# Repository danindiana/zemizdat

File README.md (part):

<div align="center">

# ZEMIZDAT

**Offline, identity-free exchange of short written "pamphlets" between strangers — over
nothing but Bluetooth broadcasts from cheap battery-powered devices.**

-success)

</div>

---

## Contents

1. [What this is](#1-what-this-is)
2. [The question, and the short answer](#2-the-question-and-the-short-answer)
3. [How it works](#3-how-it-works)
4. [What the evidence says](#4-what-the-evidence-says)
5. [What does not work (yet), and why](#5-what-does-not-work-yet-and-why)
6. [Repository map](#6-repository-map)
7. [Reproduce everything](#7-reproduce-everything)
8. [Hardware](#8-hardware)
9. [Related projects](#9-related-projects)
10. [Next step](#10-next-step)
11. [Evidence labels and honesty notes](#11-evidence-labels-and-honesty-notes)
12. [Diagrams](#12-diagrams)
13. [Status, licence, provenance](#13-status-licence-provenance)

---

## 1. What this is

ZEMIZDAT is a proposed pocket device inspired by *samizdat*, the hand-copied, hand-passed
literature of the Soviet era. Each device carries short texts — ideas, questions, arguments,
observations — called **pamphlets**. When devices come near each other they exchange pamphlets
over radio, with no internet, no phone network, no server, no account and no stable identity.
People carry pamphlets from room to room and district to district simply by walking around.

The system is **content-neutral**. It never decides what is true or acceptable. Each owner
decides what to publish, keep, delete and pass on.

This repository holds the complete pre-prototype engineering investigation
(mission brief: [`MISSION.md`](MISSION.md)):

* a formal model;
* four compared architectures;
* a byte-exact protocol specification;
* executable reference implementations in Python and C;
* a 377-run simulation campaign;
* an adversarial review;
* a hardware assessment;
* a falsifiable plan for the first hardware experiment.

> **Nothing here has been measured on hardware yet.** Every performance number is either
> *simulated* or *calculated*, and is labelled that way in the documents.

## 2. The question, and the short answer

> *Can thousands of independently operating, inexpensive, battery-powered devices exchange and
> propagate compact written information through spontaneous wireless encounters, while
> minimising duplicate storage, radio traffic, computation and dependence on centralised
> infrastructure?*

**Short answer: yes, conditionally.** The design is simpler than a mesh network, but some of
its limits are set by physics rather than engineering.

* **A connectionless broadcast "carousel" works.** There are no connections, keys, identities,
  routing or reconciliation protocol, and it serves everyone in range, including devices that
  never transmit. Simulated results:
  * 100 % of pamphlets within an hour in a hall of up to ~500 devices;
  * 95 % at 1 000 devices;
  * 98 % across six rooms of 500 people who walk between rooms;
  * 100 % across a simulated city of 3 000 people in 24 h.
* **A crowd adds receivers, not capacity.** One hall's shared airtime moves about 300 kB/s of
  pamphlet bytes. With 3 000 devices in one room, about 40 % of the collection reaches the
  average person in an hour.
* **Density-adaptive rate control is the indispensable mechanism.** Whether a real device can
  observe enough of the interference to run that control is **the largest open risk**.
* **Flooding is jamming, and interdiction beats majorities.** These are limits, not bugs, and
  they are proved or demonstrated in the repository.

Full verdict: [`09_final/EXECUTIVE_VERDICT.md`](09_final/EXECUTIVE_VERDICT.md).

## 3. How it works

### 3.1 Devices and modes

Each device has four owner-set permission bits — `RX`, `STORE`, `ORIG` (send my own), `FWD`
(send others') — exposed as three presets:

| Preset | Transmits | Receives | Privacy |
|---|---|---|---|
| **LISTEN** | never (passive scanning) | yes | discloses nothing — not even its presence |
| **EXCHANGE** | its own pamphlets | yes | discloses what it authored |
| **COURIER** | everything it carries | yes | discloses what it carries; bridges rooms and districts |

### 3.2 Content identity

A pamphlet is an immutable *canonical object* of at most 4 064 bytes (12-byte header, ordered
metadata, UTF-8 body). It is split into 220-byte chunks. Each chunk gets a truncated hash (a
*leaf*), and the pamphlet's identifier is the hash of its length and all its leaves. A small
**manifest** frame carries the leaves.

* A receiver can check **every chunk the moment it arrives**, so it can safely collect pieces
  from different senders, minutes or hours apart.
* A forged chunk is rejected on its own and can never spoil a reassembly.
* A pamphlet of up to 208 bytes is a single self-certifying frame.

### 3.3 The radio and the carousel

Frames of ≤ 236 bytes ride in anonymous, non-connectable BLE 5 *extended advertisements*, chained
three per event. Every device allowed to transmit runs a carousel with two modes:

* **Crowd mode** — many transmitters nearby. The device's event rate is scaled so the whole
  room's channel load stays near the optimum (primary-channel load ≈ 0.25, secondary ≈ 0.15).
  If it overhears someone else sending a pamphlet it holds, and the bytes match its own copy, it
  skips that pamphlet (*verified suppression*).
* **Burst mode** — eight transmitters or fewer, e.g. two people passing in a street. Contact
  time is the scarce resource, so the device listens continuously and sends fast.

Which pamphlet to send is weighted toward **items nobody nearby has sent recently**. Every
device can observe that locally, and it beat inventory-summary beacons in the simulations.

### 3.4 Receive path and storage

The receive path validates every field before touching any state, uses no heap, and holds
partial objects in at most 8 fixed staging slots. Completed objects are admitted (60 per minute
at most) and committed to a log-structured NOR-flash store. That store survives a power cut at
any byte, including during garbage collection — tested exhaustively.

### 3.5 Layers at a glance

Normative specification: [`03_protocol/ZEMIZDAT_PROTO_1.0.md`](03_protocol/ZEMIZDAT_PROTO_1.0.md)
and [`03_protocol/wire_format.md`](03_protocol/wire_format.md), which includes byte-exact worked
examples generated by the reference code.

## 4. What the evidence says

### 4.1 Executed (code in this repo, run in CI)

| Check | Result |
|---|---|
| Python reference: codec, reassembly, forged chunks, parser fuzz, storage | **31 tests pass** |
| Power cut at **every** programmed byte and erase, including GC | 0 corrupt, 0 duplicated records; at most one in-flight delete lost |
| C99 receive path vs Python on test vectors | **byte-identical** (8/8 objects, 46/46 duplicates rejected) |
| C fuzz: 2 000 000 mutated frames under AddressSanitizer + UBSan | 0 memory errors, 0 invalid completions |
| Receiver static RAM (4 slots) | 17 428 B |
| Simulator invariants (bookkeeping, determinism, LISTEN never transmits, collapse, partitions, capacity) | **14 tests pass** |
| XOR-fold inventory beacon (prior design) | one beacon reveals 100 % of a library at M = 300, 97 % at M = 1 000 → design replaced |

### 4.2 Simulated (`06_simulation`, 377 runs)

All numbers are mean completeness of honest receivers, listeners included.

| Scenario | HYBRID (this design) | rate-controlled broadcast | fixed-rate broadcast | pairwise anti-entropy |
|---|---|---|---|---|
| hall, 100 devices, 1 h | 1.00 | 1.00 | 1.00 | 0.80 (listeners 0) |
| hall, 1 000 devices, 1 h | **0.95** | 0.61 | 0.39 | 0.80 (listeners 0) |
| hall, 3 000 devices, 1 h | **0.40** | 0.36 | **0.00** | 0.28 (listeners 0) |
| 6 rooms × 500, walking, 1 h | **0.98** | 0.65 | — | 0.75 (listeners 0) |
| city of 3 000, 24 h | **1.00** (0.49 without burst mode) | 0.58 | — | 0.80 (listeners 0) |

Figures generated from the raw runs (`06_simulation/results/`):

### 4.3 Calculated (`04_mathematical_analysis/scripts`)

* An extended-advertising event is 3 × 136 µs primary pointers plus 1 064 µs per chained PDU on
  2M PHY. The optimal chain is ≈ 3 PDUs. One interference domain moves ≈ 1 500 frames/s
  (≈ 336 kB/s of pamphlet bytes), however many devices share it.
* Fixed-rate (10 Hz) advertising peaks at ~100 transmitters per domain and is dead by a few
  hundred.
* Receiving 3 000 one-KiB pamphlets in one dense hall takes **≥ 20–24 minutes even with perfect
  scheduling** at 30 % scan duty.
* Broadcast saves ≈ 100× in bits on air versus unicast — one copy per *reception tile*, not
  per person.

## 5. What does not work (yet), and why

| Limit | Kind | Where |
|---|---|---|
| Thousands in one room cannot all get everything quickly | physics (shared airtime) | [`communication_bounds.md`](04_mathematical_analysis/communication_bounds.md) |
| Rate control must sense interference it cannot decode; counting decodable neighbours only drops a 1 000-device hall from 0.82 to 0.47 | **open research question Q1** | [`RESEARCH_QUESTIONS.md`](09_final/RESEARCH_QUESTIONS.md) |
| A device that floods the channel is a jammer (20 % flooders → 0.29) | physics | [`counterexamples.md`](07_adversarial_review/counterexamples.md) |
| Anonymous publishing + finite storage + guaranteed retention is impossible | proved (Theorem D) | [`impossibility_results.md`](01_formal_model/impossibility_results.md) |
| Removing the few people who carry pamphlets between groups partitions the network, however cooperative everyone else is | proved + simulated | [`temporal_graphs.md`](04_mathematical_analysis/temporal_graphs.md) |
| Couriers are fingerprintable by what they carry; only LISTEN is library-private | proved | same |
| No device can know it holds "everything" | proved (Theorem G) | same |

## 6. Repository map

```
zemizdat/
├── README.md                       ← you are here
├── MISSION.md                      original brief (ZEMIZDAT-ARGON-1.0)
├── STATE.json                      machine-readable status, verdicts, open items
├── diagrams/                       12 diagrams (.dot source + .png + .svg)
├── 01_formal_model/                system definition, invariants I1–I10, liveness, impossibility A–J
├── 02_candidate_architectures/     broadcast, pairwise, hybrid, store-carry-forward,
│                                   comparison + verdicts, prior-art survey
├── 03_protocol/
│   ├── ZEMIZDAT_PROTO_1.0.md       normative spec
│   ├── wire_format.md              byte layouts + worked examples
│   ├── state_machine.md · synchronization.md · storage.md · security.md
│   ├── reference_py/               zmproto.py + 31 tests
│   └── reference_c/                zm_core.[ch], vectors, fuzz harness, Makefile
├── 04_mathematical_analysis/       bounds, temporal graphs, convergence, uncertainty
│   ├── scripts/                    airtime_model.py, sync_costs.py, xor_digest_attack.py
│   └── results/                    their JSON outputs
├── 05_hardware/                    UNO R4 WiFi, ESP32-S3, nRF52840, battery, BOM, dev boards
│   └── zb1/                        ZB-1 board design: spec, pinmap, BOM, Arduino variant, bring-up sketch
│       └── cad/                    KiCad 7 schematic + routed 4-layer PCB, Gerbers, STEP, renders, generators
├── 06_simulation/                  simulator.py, run_experiments.py, analyze.py,
│                                   tests/, configs/, results/ (runs.jsonl, summary.md, figures)
├── 07_adversarial_review/          threat model, 15 counterexamples, failure matrix, mitigations
├── 08_verification/                hardware test plan E1–E7, properties, acceptance tests, gaps
└── 09_final/                       verdict, architecture decision, spec index, research
                                    questions, prototype plan, next action, Gemini audit
```

**Suggested reading order:**

1. `09_final/EXECUTIVE_VERDICT.md`
2. `09_final/ARCHITECTURE_DECISION.md`
3. `03_protocol/ZEMIZDAT_PROTO_1.0.md`
4. `04_mathematical_analysis/convergence.md`
5. `07_adversarial_review/counterexamples.md`
6. `08_verification/test_plan.md`

## 7. Reproduce everything

Requirements: Python ≥ 3.11, `numpy ≥ 2`, `matplotlib`, `pytest`, and gcc or clang with
sanitizers; Graphviz only to re-render the diagrams.

```bash
git clone https://github.com/danindiana/zemizdat && cd zemizdat
pip install "numpy>=2" matplotlib pytest

# protocol reference (≈ 20 s)
(cd 03_protocol/reference_py && python -m pytest -q)

# C receive path: Python-generated vectors + 2M-frame sanitizer fuzz (≈ 1 min)
(cd 03_protocol/reference_c && make test)

# analytical models
(cd 04_mathematical_analysis/scripts && python airtime_model.py && python sync_costs.py && python xor_digest_attack.py)

# simulator tests (≈ 30 s), then the full campaign (≈ 6–8 CPU-hours, resumable)
cd 06_simulation
python -m pytest -q tests
python run_experiments.py --jobs 2     # appends to results/runs.jsonl, skips finished runs
python analyze.py                       # regenerates results/summary.md and figures

# one ad-hoc run
python simulator.py --N 1000 --T 1800 --strategy HYBRID --sdb false

# diagrams
cd ../diagrams && for f in *.dot; do dot -Tpng -Gdpi=160 "$f" -o "${f%.dot}.png" && dot -Tsvg "$f" -o "${f%.dot}.svg"; done
```

## 8. Hardware

| Option | Verdict | Why |
|---|---|---|
| Arduino UNO R4 WiFi | **reject for production**; bench helper | 32 KB SRAM on the RA4M1 and no radio; its ESP32-S3 can be flashed directly, and the RA4M1 can drive power-cut tests |
| ESP32-S3 | **conditional** (prototype) | fits easily; module datasheet gives BLE receive at 93 mA (peak), so ~2 days on 2000 mAh in a crowd |
| nRF52840 + 8 MB SPI NOR | **conditional** (production candidate) | radio ≈ 6.3 mA receive / 6.4 mA transmit at 0 dBm (datasheet); runs directly from a Li-ion cell |
| nRF54L15 | unresolved | datasheet figures not yet reviewed |

* Board shortlist with prices: [`05_hardware/dev_boards.md`](05_hardware/dev_boards.md).
  Best value is the Seeed XIAO nRF52840.
* Battery arithmetic, clearly marked as estimates:
  [`05_hardware/battery_budget.md`](05_hardware/battery_budget.md).

### ZB-1 development board (design, not yet built)

[`05_hardware/zb1/`](05_hardware/zb1/README.md) is a purpose-built Feather-size board:

* ESP32-S3-MINI-1-N8 (BLE 5 extended advertising, Wi-Fi, native USB, 8 MB NOR for the pamphlet log);
* USB-C LiPo charging (BQ21040) with a load-sharing power path and a 2 µA-Iq LDO;
* a power-switched 4-bit microSD slot (SDSC/SDHC/SDXC up to 2 TB; exFAT via SdFat or FAT32 reformat);
* test hooks for energy (E6) and power-cut (E7) experiments;
* ≈ $10–13 at qty 100 [estimate].

It is programmable from the Arduino IDE: a `boards.txt` entry and variant are included, and the
bring-up sketch (anonymous extended advertising + passive scan through `zm_core.c`) compiles.
Because ESP32-S3 BLE receive costs 93 mA versus 6.26 mA on the nRF52840, the design document
recommends an nRF52840-based ZB-2 for a pocket device.

The full CAD package is in [`05_hardware/zb1/cad/`](05_hardware/zb1/cad/README.md). It contains:

* a KiCad 7 schematic and a routed 4-layer PCB;
* Gerbers, drill, pick-and-place and BOM;
* a STEP model of the assembled board;
* the scripts that generate all of it from one design database.

## 9. Related projects

No open-source project found combines receive-only participation, no identity on air, and
content-addressed microcontroller firmware. The closest relatives are Rumble (epidemic
store-carry-forward on Android), Serval Rhizome/LBARD (content-addressed bundle sync over
constrained radios), bitchat (BLE mesh chat), Meshtastic and MeshCore (LoRa microcontroller
firmware), Reticulum LXMF (propagation nodes), and OpenHaystack (passive pickup of BLE
advertisements by bystanders).

Lessons from the security failures of comparable apps, notably Bridgefy and early bitchat, are
in [`02_candidate_architectures/prior_art.md`](02_candidate_architectures/prior_art.md).

## 10. Next step

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
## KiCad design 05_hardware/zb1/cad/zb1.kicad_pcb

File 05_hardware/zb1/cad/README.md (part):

# ZB-1 CAD package — KiCad 7 schematic, 4-layer PCB, fab outputs, 3D model

This folder holds the complete electronic CAD for the [ZB-1 development board](../README.md):

* a KiCad 7 project with schematic and routed 4-layer PCB;
* Gerbers, drill, pick-and-place and BOM;
* a STEP model of the assembled board, plus rendered views.

Everything is generated by scripts from one design database (`scripts/zb1_design.py`), so the
board can be rebuilt and every number below re-checked.

> **Licence:**
> * The ZB-1 hardware design is © 2026 Benjamin W. Denio under the
>   [CERN Open Hardware Licence v2 – Permissive](../../../LICENSES/CERN-OHL-P-2.0.txt).
> * The generator scripts in `scripts/` are under [Apache-2.0](../../../LICENSES/Apache-2.0.txt).
> * The Espressif module footprint and STEP model keep their CC-BY-SA 4.0 licence ([`lib/ATTRIBUTION.md`](lib/ATTRIBUTION.md)).
>
> If you modify the design and share it, say so in your copy (CERN-OHL-P §3.3).

> **Status: design files, not a proven board.** Nothing here has been fabricated, assembled or
> powered. The layout was placed by script and routed by an autorouter. DRC results are reported
> honestly in §5, including the items that still need a human. A qualified layout review is
> required before ordering boards; see the checklist in §7.

| | |
|---|---|
| Board | 50.8 × 22.86 mm (Adafruit Feather outline), 1.5 mm corner radius, 1.6 mm FR-4 |
| Layers | 4: F.Cu signal / In1 solid GND plane / In2 signal + GND fill / B.Cu signal + GND fill |
| Parts | 69 electrical parts + 2 mounting holes placed (7 of them DNP by default), top and bottom side |
| Routing | 1 127 track segments, 149 vias; 0.15 mm signal / 0.3 mm power / 0.2 mm USB tracks, 0.5/0.25 mm vias |
| Antenna | module antenna flush with the board edge; copper keep-out on all four layers past x = 45.4 mm |
| Netlist | schematic netlist checked pin by pin against the design database: **OK** — 69 components, 57 nets, 264 pin connections; the PCB pads were cross-checked the same way (0 mismatches) |
| DRC | **0 unconnected, 0 clearance / hole / short errors.** 8 mechanical items waived (mounting-hole courtyards, edge-mount microSD shell), 94 cosmetic warnings (silkscreen, library-copy differences) — see §5 |

## 1. Files

| Path | What it is |
|---|---|
| `zb1.kicad_pro`, `zb1.kicad_sch`, `zb1.kicad_pcb` | KiCad 7 project: open `zb1.kicad_pro` in KiCad 7.0 or newer |
| `lib/zb1.kicad_sym` | project symbols for parts KiCad 7 lacks: BQ21040, RT9080-33, DW01A, FS8205A, MAX17048 |
| `lib/zb1.pretty/ESP32-S3-MINI-1.kicad_mod` | module footprint from [espressif/kicad-libraries](https://github.com/espressif/kicad-libraries) (CC-BY-SA 4.0 with the KiCad design exception) |
| `lib/3dmodels/` | Espressif module STEP model, plus simple dimensioned envelope bodies for parts without a KiCad 3D model (USB-C, microSD, both JST connectors, KMR2 switches, crystal) |
| `fab/zb1_gerbers.zip` | Gerber X2 (11 layers) + Excellon drill (PTH and NPTH separate): upload this to a PCB fab |
| `fab/zb1_bom.csv` | grouped BOM with MPNs; DNP lines marked |
| `fab/zb1_pos.csv` | pick-and-place centroids, both sides, mm (DNP and through-hole parts excluded) |
| `docs/zb1_schematic.pdf` | schematic, one A2 sheet in seven titled blocks |
| `docs/zb1_assembly_top.pdf`, `docs/zb1_assembly_bottom.pdf` | assembly drawings (fab layer with every reference) |
| `docs/*drl_map.pdf` | drill maps |
| `3d/zb1.step` | whole assembly for enclosure/mechanical CAD (FreeCAD, Fusion, Onshape, SolidWorks) |
| `images/` | schematic PNG, per-copper-layer plots, board-surface images, 3D renders |
| `reports/drc.rpt` | full KiCad DRC report |
| `reports/netlist_check.txt` | schematic-vs-design-database check |
| `scripts/` | the generators (§6) |
| `build.sh` | rebuilds everything above from `scripts/zb1_design.py` |

## 2. Schematic

The schematic implements exactly the circuit in [`../README.md`](../README.md) §3–§5. It is drawn
in a "label per pin" style: every pin gets a short stub with its net label. It is generated from
`zb1_design.py`, so edit that file and regenerate rather than editing the schematic by hand.
`reports/netlist_check.txt` confirms that the netlist KiCad exports from the schematic matches the
database:
* every component present, with the designed footprint and value;
* every designed pin connection present;
* no extra connections.

Changes from the earlier text description, made while drawing it:

* **BQ21040 pinout** checked against the TI datasheet: 1 TS, 2 OUT, 3 /CHG, 4 ISET, 5 VSS, 6 IN.
  TS must not float (that enters a test mode), so R4 = 10 kΩ to GND stays fitted.
* **USBLC6-2SC6** is flow-through: pins 1/6 and 3/4 are the same line, so each data line is one net.
* **TPS22917 QOD** is tied to VOUT so the card's supply is actively discharged when switched off.
  CT is left open for the fastest turn-on.
* **Battery connector:** J3 pin 1 = BAT−, pin 2 = BAT+. Check this against your cell: JST-PH
  LiPo leads have no polarity standard, and a reversed cell will destroy the charger.
* **Optional cell protection:** U6 DW01A and Q2 FS8205A are drawn and laid out but DNP. SJ2
  bridges BATN to GND. Cut SJ2 if you fit them.

## 3. PCB

| Top | Bottom (seen from below) |
|---|---|
|  |  |

**Top side**
* ESP32-S3-MINI-1 with its antenna at the right-hand edge.
* USB-C at the left, with ESD protection.
* Charger and power-path parts.
* Vertical JST-PH battery jack.
* RESET and BOOT buttons.
* 32.768 kHz crystal placed against the module's XTAL_32K pins.
* Charge and user LEDs.
* Feather headers (supplied loose).

**Bottom side**
* microSD socket, slot at the USB end.
* SD load switch and pull-ups.
* LDO and the current-measurement jumper SJ1 (marked `CUT=I`).
* Battery divider.
* STEMMA-QT connector.
* Test pads TP1–TP5 for a pogo-pin fixture: TP_EN, VBAT, VSYS, 3V3, GND.
* Optional protection and fuel-gauge footprints.

| F.Cu | In1 (GND plane) |
|---|---|
|  |  |
| **In2** | **B.Cu** |
|  |  |

Layout decisions:

* **Antenna:**
  * The module sits flush with the board edge.
  * A rule area bans copper pour, tracks and vias on all four layers under and beyond the antenna (x > 45.4 mm).
  * No parts sit on either side in that zone.
* **No tracks under the module's centre on F.Cu.** A rule area 1.4 mm inside the pad ring allows
  only vias and the GND pour there. Pads may take a short inward stub to a via (standard practice
  for LGA modules, and needed to escape 0.85 mm-pitch pads). The centre GND pad has nine via-in-pad
  stitches to the In1 plane; specify them filled and capped, or tented from the bottom.
* **GND:**
  * In1 is an unbroken plane.
  * F.Cu, In2 and B.Cu are GND-filled with thermal reliefs.
  * Every SMD GND pad that had room received its own via to the plane before routing.
* **Mounting holes:**
  * Only the two antenna-end Feather holes (M2) are present.
  * The two USB-end holes collide with the microSD socket on the bottom and were omitted — a deliberate deviation from the Feather specification.
  * The antenna-end holes touch the module courtyard, exactly as on Adafruit's own ESP32-S3 Feather.
* **Silkscreen:**
  * Feather pin names on the top.
  * Battery polarity marks, button names and board name on the top.
  * Passive references only on the assembly drawings, to keep the silkscreen legible.
  * No serial numbers or unique identifiers ([`../README.md`](../README.md) R8).

### Design rules used

Set for a standard 4-layer prototype service (JLCPCB/PCBWay class): track/space 0.15/0.15 mm
signal (fab minimum is typically 0.09–0.1 mm), 0.3 mm power, via 0.5 mm pad / 0.25 mm drill,
hole-to-copper 0.2 mm, copper-to-edge 0.25 mm. **Check the 0.25 mm drill against your fab's
standard (not premium) capability before ordering.**

## 4. 3D model

`3d/zb1.step` contains the bare board and every fitted part:
* the real Espressif module model;
* KiCad library models for the passives, ICs and headers;
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
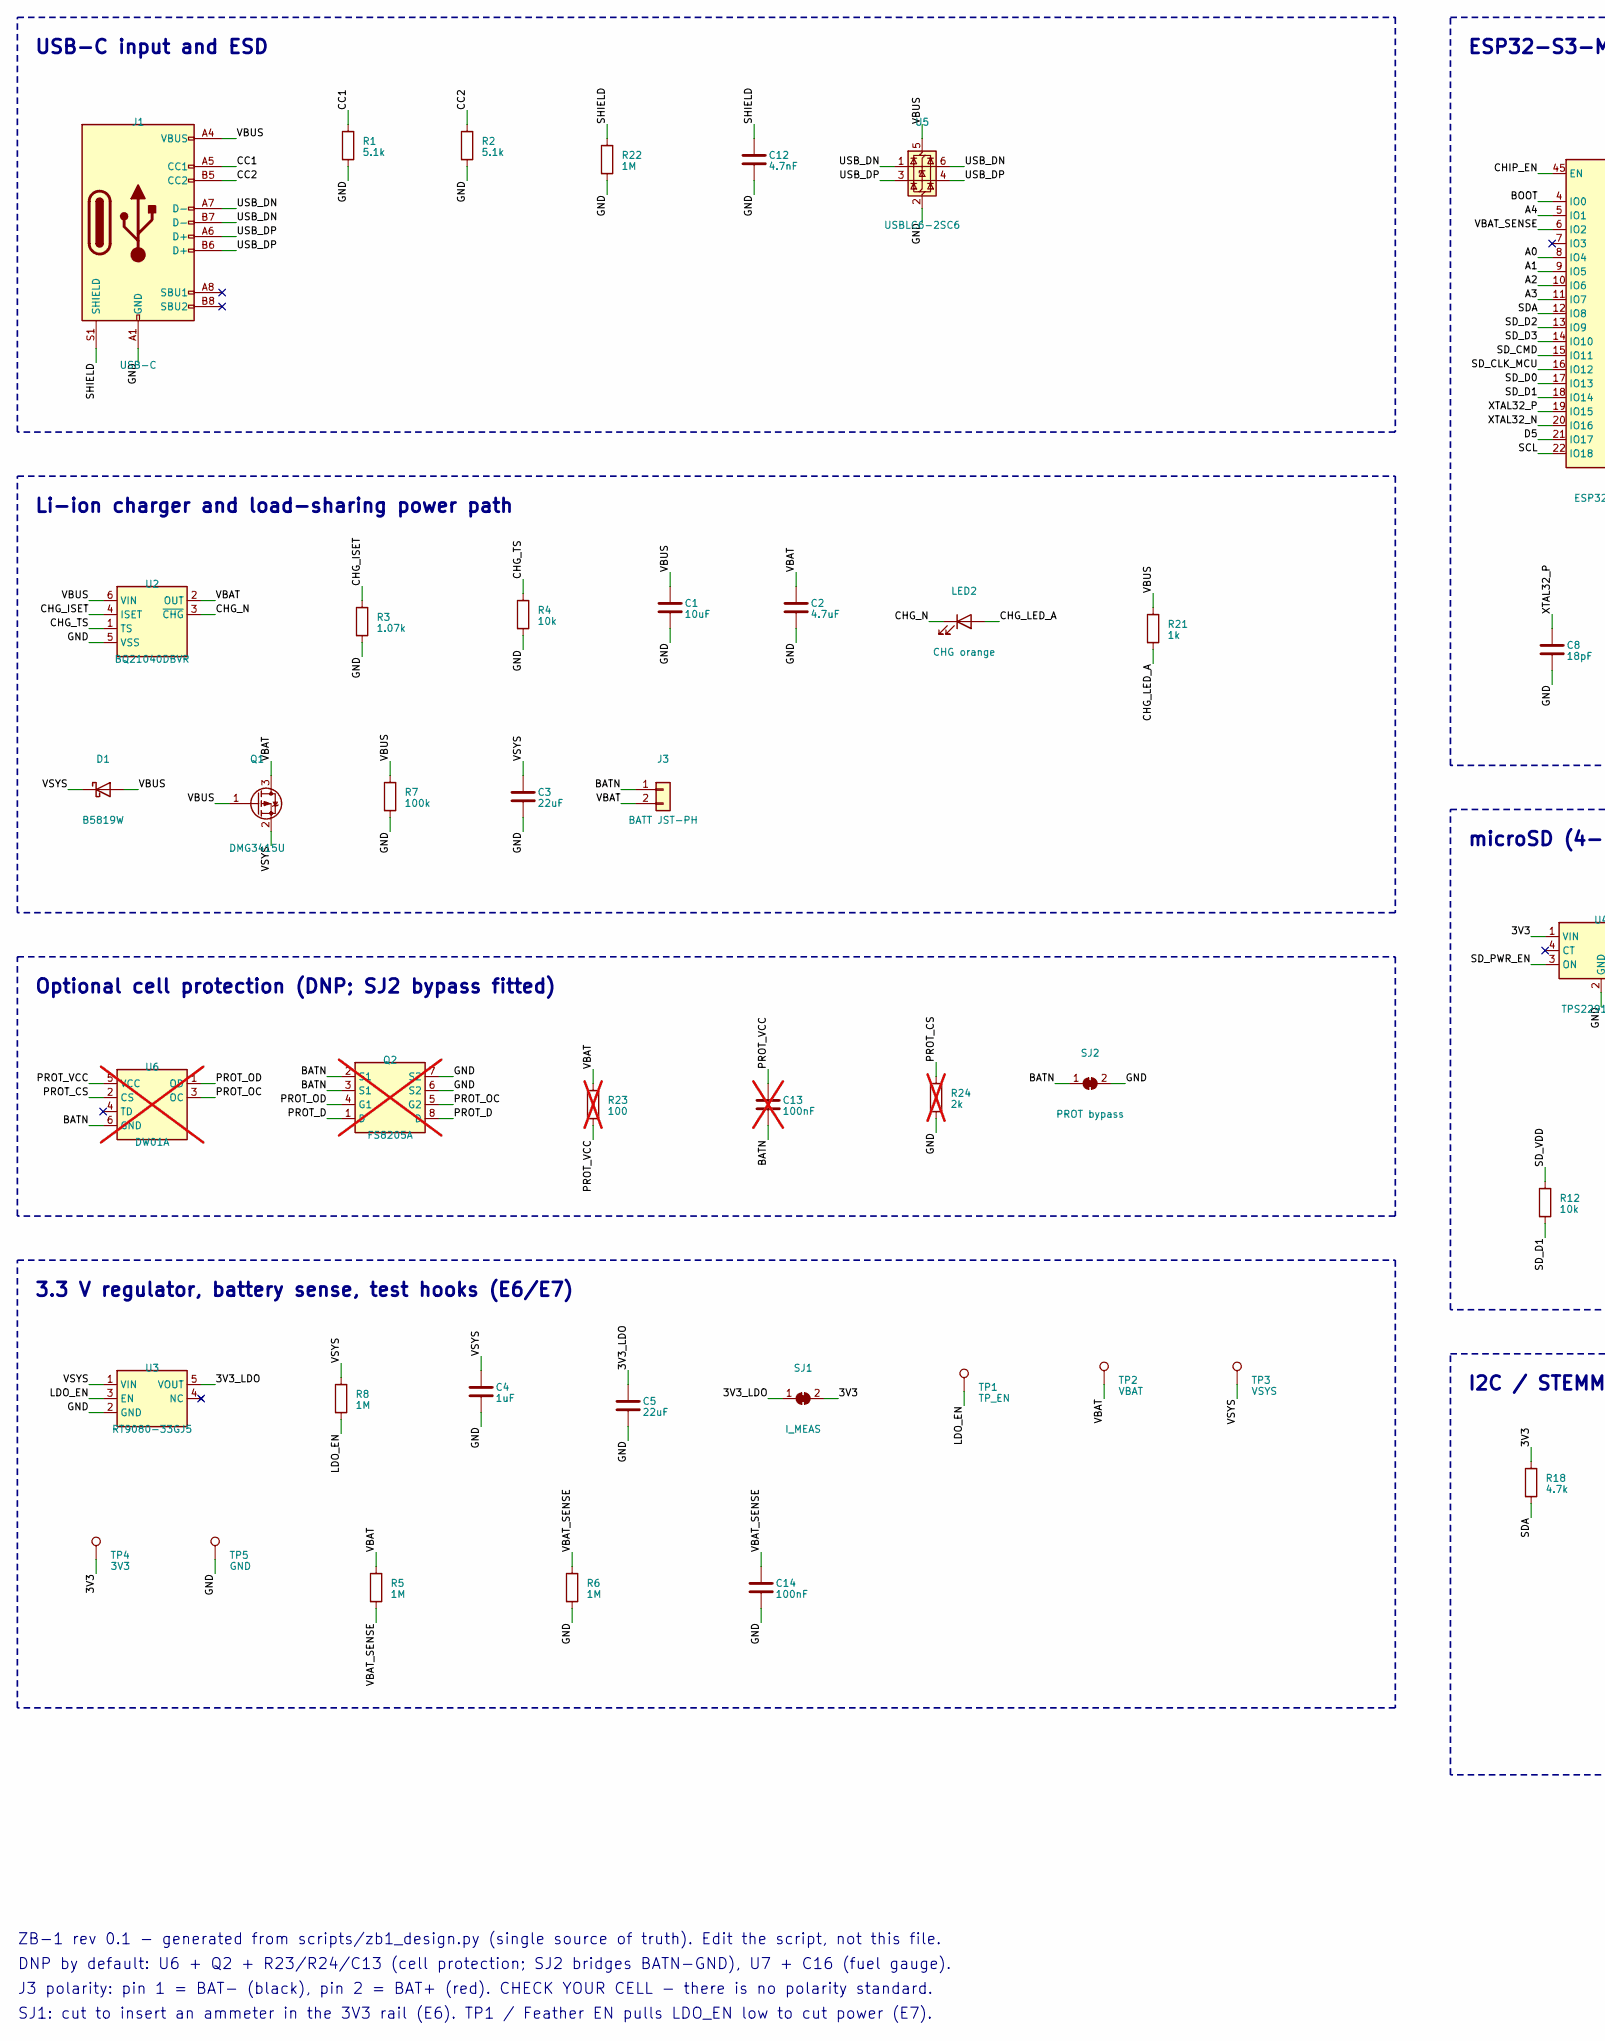
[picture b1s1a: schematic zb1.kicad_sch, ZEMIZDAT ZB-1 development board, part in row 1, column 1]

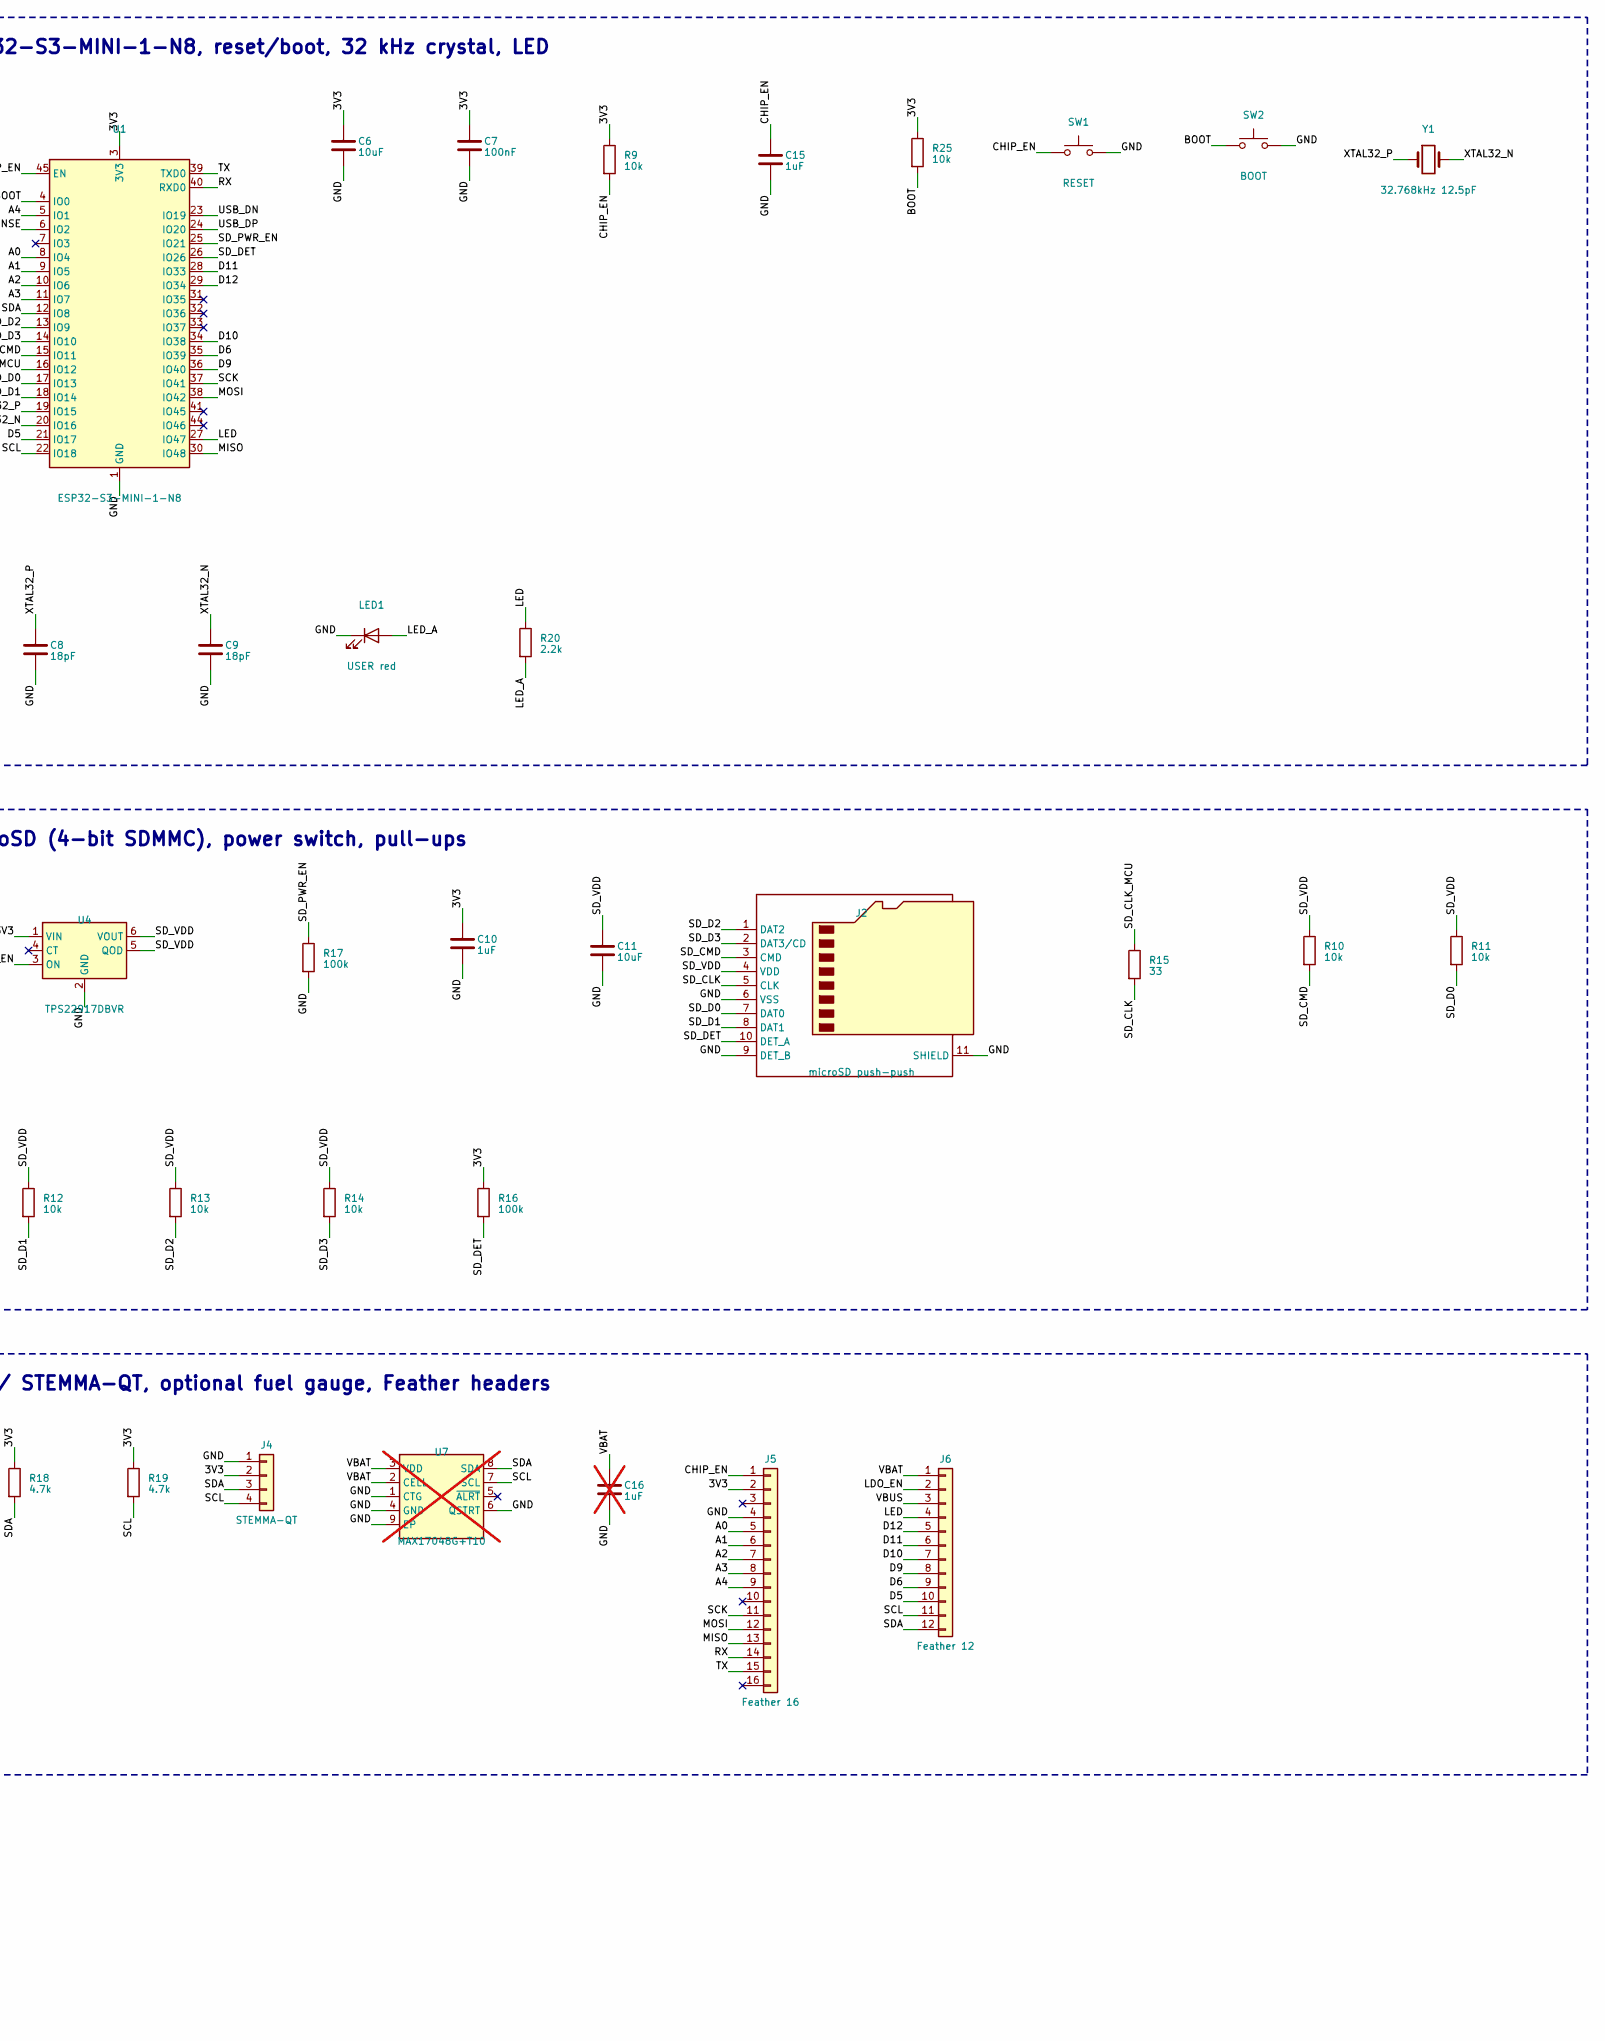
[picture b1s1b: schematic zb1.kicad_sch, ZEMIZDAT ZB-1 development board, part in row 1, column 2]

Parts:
C1, C6, C11: 10uF; C_0603_1608Metric; MPN 10uF X5R/X7R
C2: 4.7uF; C_0603_1608Metric; MPN 4.7uF X5R/X7R
C3, C5: 22uF; C_0805_2012Metric; MPN 22uF X5R/X7R
C4, C10, C15: 1uF; C_0402_1005Metric; MPN 1uF X5R/X7R
C7, C14: 100nF; C_0402_1005Metric; MPN 100nF X5R/X7R
C8, C9: 18pF; C_0402_1005Metric; MPN 18pF C0G
C12: 4.7nF; C_0402_1005Metric; MPN 4.7nF X5R/X7R
C13: 100nF; C_0402_1005Metric; MPN 100nF X5R/X7R; not fitted
C16: 1uF; C_0402_1005Metric; MPN 1uF X5R/X7R; not fitted
D1: B5819W; D_SOD-123; MPN B5819W SOD-123
J1: USB-C; USB_C_Receptacle_HRO_TYPE-C-31-M-12; MPN HRO TYPE-C-31-M-12
J2: microSD push-push; microSD_HC_Hirose_DM3AT-SF-PEJM5; MPN Hirose DM3AT-SF-PEJM5
J3: BATT JST-PH; JST_PH_B2B-PH-SM4-TB_1x02-1MP_P2.00mm_Vertical; MPN JST B2B-PH-SM4-TB
J4: STEMMA-QT; JST_SH_BM04B-SRSS-TB_1x04-1MP_P1.00mm_Vertical; MPN JST BM04B-SRSS-TB
J5: Feather 16; PinHeader_1x16_P2.54mm_Vertical; MPN 1x16 2.54mm header (ship loose)
J6: Feather 12; PinHeader_1x12_P2.54mm_Vertical; MPN 1x12 2.54mm header (ship loose)
LED1: USER red; LED_0603_1608Metric; MPN red 0603 LED
LED2: CHG orange; LED_0603_1608Metric; MPN orange 0603 LED
Q1: DMG3415U; SOT-23; MPN Diodes DMG3415U-7
Q2: FS8205A; TSSOP-8_4.4x3mm_P0.65mm; MPN Fortune FS8205A; not fitted
R1, R2: 5.1k; R_0402_1005Metric; MPN 5.1k 1% 0402
R3: 1.07k; R_0402_1005Metric; MPN 1.07k 1% 0402
R4: 10k; R_0402_1005Metric; MPN 10k 1% (or 10k NTC on the cell)
R5, R6, R8, R22: 1M; R_0402_1005Metric; MPN 1M 1% 0402
R7, R16, R17: 100k; R_0402_1005Metric; MPN 100k 1% 0402
R9, R10, R11, R12, R13, R14, R25: 10k; R_0402_1005Metric; MPN 10k 1% 0402
R15: 33; R_0402_1005Metric; MPN 33 1% 0402
R18, R19: 4.7k; R_0402_1005Metric; MPN 4.7k 1% 0402
R20: 2.2k; R_0402_1005Metric; MPN 2.2k 1% 0402
R21: 1k; R_0402_1005Metric; MPN 1k 1% 0402
R23: 100; R_0402_1005Metric; MPN 100 1% 0402; not fitted
R24: 2k; R_0402_1005Metric; MPN 2k 1% 0402; not fitted
SJ1: I_MEAS; SolderJumper-2_P1.3mm_Bridged_RoundedPad1.0x1.5mm; MPN (PCB) cut to measure current
SJ2: PROT bypass; SolderJumper-2_P1.3mm_Bridged_RoundedPad1.0x1.5mm; MPN (PCB) cut if U6/Q2 fitted
SW1: RESET; SW_Push_1P1T_NO_CK_KMR2; MPN C&K KMR221GLFS
SW2: BOOT; SW_Push_1P1T_NO_CK_KMR2; MPN C&K KMR221GLFS
TP1: TP_EN; TestPoint_Pad_D1.0mm; MPN (PCB)
TP2: VBAT; TestPoint_Pad_D1.0mm; MPN (PCB)
TP3: VSYS; TestPoint_Pad_D1.0mm; MPN (PCB)
TP4: 3V3; TestPoint_Pad_D1.0mm; MPN (PCB)
TP5: GND; TestPoint_Pad_D1.0mm; MPN (PCB)
U1: ESP32-S3-MINI-1-N8; ESP32-S3-MINI-1; MPN Espressif ESP32-S3-MINI-1-N8
U2: BQ21040DBVR; SOT-23-6; MPN TI BQ21040DBVR
U3: RT9080-33GJ5; SOT-23-5; MPN Richtek RT9080-33GJ5
U4: TPS22917DBVR; SOT-23-6; MPN TI TPS22917DBVR
U5: USBLC6-2SC6; SOT-23-6; MPN ST USBLC6-2SC6
U6: DW01A; SOT-23-6; MPN Fortune DW01A; not fitted
U7: MAX17048G+T10; TDFN-8-1EP_2x2mm_P0.5mm_EP0.8x1.2mm; MPN Analog Devices MAX17048G+T10; not fitted
Y1: 32.768kHz 12.5pF; Crystal_SMD_3215-2Pin_3.2x1.5mm; MPN Epson FC-135 32.768kHz 12.5pF

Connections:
3V3: C6.1, C7.1, C10.1, J4.2, J5.2, R9.1, R16.1, R18.1, R19.1, R25.1, SJ1.2 (B), TP4.1, U1.3 (3V3), U4.1 (VIN)
3V3_LDO: C5.1, SJ1.1 (A), U3.5 (VOUT)
A0: J5.5, U1.8 (IO4)
A1: J5.6, U1.9 (IO5)
A2: J5.7, U1.10 (IO6)
A3: J5.8, U1.11 (IO7)
A4: J5.9, U1.5 (IO1)
BATN: C13.2, J3.1, Q2.2 (S1), Q2.3 (S1), SJ2.1 (A), U6.6 (GND)
BOOT: R25.2, SW2.1, U1.4 (IO0)
CC1: J1.A5 (CC1), R1.1
CC2: J1.B5 (CC2), R2.1
CHG_ISET: R3.1, U2.4 (ISET)
CHG_LED_A: LED2.2 (A), R21.2
CHG_N: LED2.1 (K), U2.3 (~CHG)
CHG_TS: R4.1, U2.1 (TS)
CHIP_EN: C15.1, J5.1, R9.2, SW1.1, U1.45 (EN)
D5: J6.10, U1.21 (IO17)
D6: J6.9, U1.35 (IO39)
D9: J6.8, U1.36 (IO40)
D10: J6.7, U1.34 (IO38)
D11: J6.6, U1.28 (IO33)
D12: J6.5, U1.29 (IO34)
GND: C1.2, C2.2, C3.2, C4.2, C5.2, C6.2, C7.2, C8.2, C9.2, C10.2, C11.2, C12.2, C14.2, C15.2, C16.2, J1.A1 (GND), J1.A12 (GND), J1.B1 (GND), J1.B12 (GND), J2.6 (VSS), J2.9 (DET_B), J2.11 (SHIELD), J4.1, J5.4, LED1.1 (K), Q2.6 (S2), Q2.7 (S2), R1.2, R2.2, R3.2, R4.2, R6.2, R7.2, R17.2, R22.2, R24.2, SJ2.2 (B), SW1.2, SW2.2, TP5.1, U1.1 (GND), U1.2 (GND), U1.42 (GND), U1.43 (GND), U1.46 (GND), U1.47 (GND), U1.48 (GND), U1.49 (GND), U1.50 (GND), U1.51 (GND), U1.52 (GND), U1.53 (GND), U1.54 (GND), U1.55 (GND), U1.56 (GND), U1.57 (GND), U1.58 (GND), U1.59 (GND), U1.60 (GND), U1.61 (GND), U1.62 (GND), U1.63 (GND), U1.64 (GND), U1.65 (GND), U2.5 (VSS), U3.2 (GND), U4.2 (GND), U5.2 (GND), U7.1 (CTG), U7.4 (GND), U7.6 (QSTRT), U7.9 (EP)
LDO_EN: J6.2, R8.2, TP1.1, U3.3 (EN)
LED: J6.4, R20.1, U1.27 (IO47)
LED_A: LED1.2 (A), R20.2
MISO: J5.13, U1.30 (IO48)
MOSI: J5.12, U1.38 (IO42)
PROT_CS: R24.1, U6.2 (CS)
PROT_D: Q2.1 (D), Q2.8 (D)
PROT_OC: Q2.5 (G2), U6.3 (OC)
PROT_OD: Q2.4 (G1), U6.1 (OD)
PROT_VCC: C13.1, R23.2, U6.5 (VCC)
RX: J5.14, U1.40 (RXD0)
SCK: J5.11, U1.37 (IO41)
SCL: J4.4, J6.11, R19.2, U1.22 (IO18), U7.7 (SCL)
SDA: J4.3, J6.12, R18.2, U1.12 (IO8), U7.8 (SDA)
SD_CLK: J2.5 (CLK), R15.2
SD_CLK_MCU: R15.1, U1.16 (IO12)
SD_CMD: J2.3 (CMD), R10.2, U1.15 (IO11)
SD_D0: J2.7 (DAT0), R11.2, U1.17 (IO13)
SD_D1: J2.8 (DAT1), R12.2, U1.18 (IO14)
SD_D2: J2.1 (DAT2), R13.2, U1.13 (IO9)
SD_D3: J2.2 (DAT3/CD), R14.2, U1.14 (IO10)
SD_DET: J2.10 (DET_A), R16.2, U1.26 (IO26)
SD_PWR_EN: R17.1, U1.25 (IO21), U4.3 (ON)
SD_VDD: C11.1, J2.4 (VDD), R10.1, R11.1, R12.1, R13.1, R14.1, U4.5 (QOD), U4.6 (VOUT)
SHIELD: C12.1, J1.S1 (SHIELD), R22.1
TX: J5.15, U1.39 (TXD0)
USB_DN: J1.A7 (D-), J1.B7 (D-), U1.23 (IO19), U5.1 (I/O1), U5.6 (I/O1)
USB_DP: J1.A6 (D+), J1.B6 (D+), U1.24 (IO20), U5.3 (I/O2), U5.4 (I/O2)
VBAT: C2.1, C16.1, J3.2, J6.1, Q1.3 (D), R5.1, R23.1, TP2.1, U2.2 (OUT), U7.2 (CELL), U7.3 (VDD)
VBAT_SENSE: C14.1, R5.2, R6.1, U1.6 (IO2)
VBUS: C1.1, D1.2 (A), J1.A4 (VBUS), J1.A9 (VBUS), J1.B4 (VBUS), J1.B9 (VBUS), J6.3, Q1.1 (G), R7.1, R21.1, U2.6 (VIN), U5.5 (VBUS)
VSYS: C3.1, C4.1, D1.1 (K), Q1.2 (S), R8.1, TP3.1, U3.1 (VIN)
XTAL32_N: C9.1, U1.20 (IO16), Y1.2
XTAL32_P: C8.1, U1.19 (IO15), Y1.1

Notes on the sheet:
USB-C input and ESD
Li-ion charger and load-sharing power path
Optional cell protection (DNP; SJ2 bypass fitted)
3.3 V regulator, battery sense, test hooks (E6/E7)
ESP32-S3-MINI-1-N8, reset/boot, 32 kHz crystal, LED
microSD (4-bit SDMMC), power switch, pull-ups
I2C / STEMMA-QT, optional fuel gauge, Feather headers
ZB-1 rev 0.1 - generated from scripts/zb1_design.py (single source of truth). Edit the script, not this file.
DNP by default: U6 + Q2 + R23/R24/C13 (cell protection; SJ2 bridges BATN-GND), U7 + C16 (fuel gauge).
J3 polarity: pin 1 = BAT- (black), pin 2 = BAT+ (red). CHECK YOUR CELL - there is no polarity standard.
SJ1: cut to insert an ammeter in the 3V3 rail (E6). TP1 / Feather EN pulls LDO_EN low to cut power (E7).

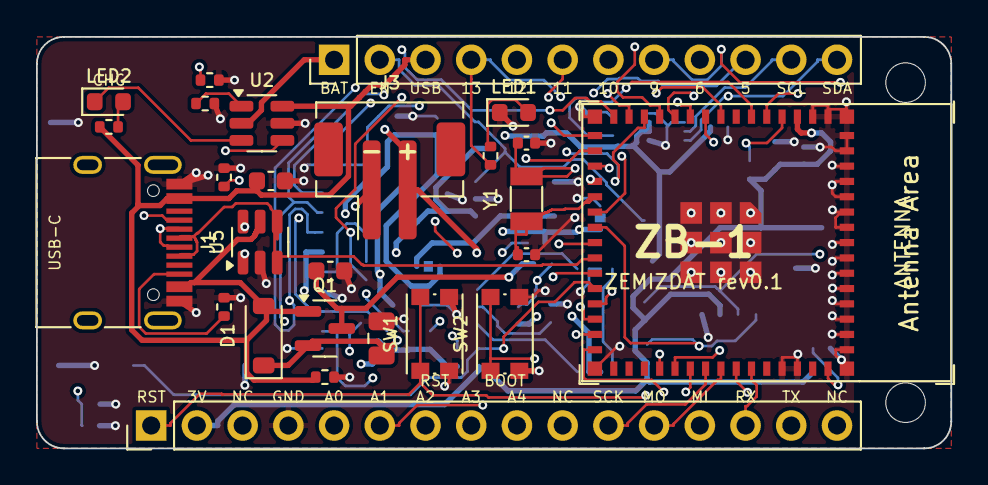
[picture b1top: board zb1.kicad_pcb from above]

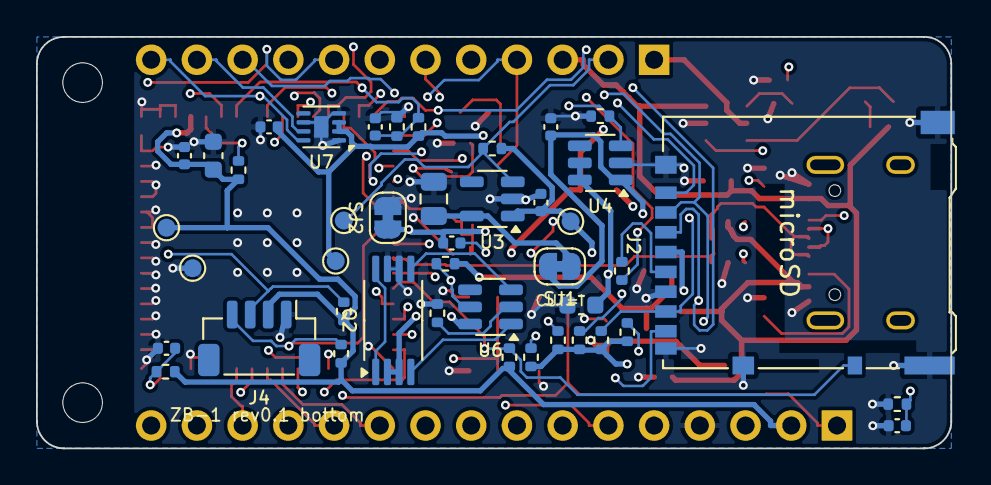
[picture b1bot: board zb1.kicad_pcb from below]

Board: 4 copper layers, 50.8 x 22.9 mm, 71 parts (43 on the bottom side), 57 nets.

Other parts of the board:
H3, H4: M2; MountingHole_2.2mm_M2

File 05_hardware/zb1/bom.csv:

ref,qty,part,package,function,unit_usd_qty100,price_basis,populate
U1,1,ESP32-S3-MINI-1-N8,module 15.4x20.5 mm,MCU + BLE 5 + Wi-Fi + 8 MB flash + PCB antenna,2.90,estimate,yes
U2,1,TI BQ21040DBVR,SOT-23-6,1-cell Li-ion linear charger (ISET 500 mA; TS input; /CHG),0.55,estimate,yes
U3,1,Richtek RT9080-33GJ5,SOT-23-5,3.3 V 600 mA LDO; 2 uA Iq; EN broken out for power-cut tests,0.20,estimate,yes
U4,1,TI TPS22917DBVR,SOT-23-6,microSD power load switch (1 uA leakage off),0.30,estimate,yes
U5,1,ST USBLC6-2SC6,SOT-23-6,USB D+/D- ESD protection,0.12,estimate,yes
U6,1,Fortune DW01A,SOT-23-6,battery protection controller (only if cell has no PCM),0.04,estimate,optional
Q2,1,FS8205A,TSSOP-8,dual N-MOSFET for DW01A,0.05,estimate,optional
U7,1,Analog Devices MAX17048G+T10,TDFN-8 2x2,fuel gauge (I2C) - adds 23 uA; ADC divider is default,1.20,estimate,DNP
Q1,1,DMG3415U,SOT-23,P-MOSFET load-sharing power path (battery -> VSYS when USB absent),0.05,estimate,yes
D1,1,B5819W (or SS14),SOD-123,Schottky VBUS -> VSYS,0.03,estimate,yes
J1,1,USB-C 16-pin receptacle (USB 2.0),SMD mid-mount,power + native USB,0.25,estimate,yes
J2,1,microSD push-push socket with card-detect,SMD,storage archive (SDSC/SDHC/SDXC),0.30,estimate,yes
J3,1,JST PH 2-pin vertical (B2B-PH-SM4-TB),SMD,LiPo battery (top entry; side entry does not fit beside USB-C),0.06,estimate,yes
J4,1,JST SH 4-pin vertical (BM04B-SRSS-TB; STEMMA-QT/Qwiic),SMD,I2C expansion (bottom side),0.10,estimate,yes
J5/J6,2,1x16 and 1x12 2.54 mm headers,TH,Feather headers,0.20,estimate,ship loose
Y1,1,32.768 kHz crystal 12.5 pF,3215,BLE low-power clock,0.15,estimate,yes
SW1/SW2,2,tactile switch 3x4 mm,SMD,RESET and BOOT,0.04,estimate,yes
LED1,1,red LED,0603,user LED (GPIO47),0.01,estimate,yes
LED2,1,orange LED,0603,charge (/CHG),0.01,estimate,yes
R1/R2,2,5.1k 1%,0402,USB-C CC1/CC2 pull-downs (sink),0.002,estimate,yes
R3,1,1.07k 1%,0402,BQ21040 ISET -> ~500 mA (K_ISET 540 A·ohm; check datasheet),0.002,estimate,yes
R4,1,10k 1% (or 10k NTC on cell),0402,BQ21040 TS,0.002,estimate,yes
R5/R6,2,1M 1%,0402,VBAT divider,0.002,estimate,yes
R7,1,100k,0402,Q1 gate pull-down,0.002,estimate,yes
R8,1,1M,0402,LDO EN pull-up (TP_EN pad pulls low for E7 power cuts),0.002,estimate,yes
R9-R14,6,10k,0402,SD CMD/D0-D3 pull-ups + EN pull-up,0.002,estimate,yes
R15,1,33R,0402,SD_CLK series,0.002,estimate,yes
R16/R17,2,100k,0402,SD_DETECT pull-up; SD_PWR_EN pull-down,0.002,estimate,yes
R18/R19,2,4.7k,0402,I2C pull-ups,0.002,estimate,yes
R20/R21,2,2.2k / 1k,0402,LED resistors,0.002,estimate,yes
C*,~16,MLCC 100nF / 1uF / 10uF / 22uF,0402-0805,decoupling + bulk (22uF on VSYS and 3V3 for TX bursts; 10uF on SD_VDD),0.20 total,estimate,yes
SJ1,1,solder jumper (closed),pads,cut to insert ammeter between LDO and module (E6),0,-,yes
PCB,1,4-layer 50.8 x 22.86 mm FR-4 1.6 mm ENIG,-,Feather form factor,1.60,estimate,yes
ASSY,1,SMT assembly (one side),-,-,2.50,estimate,-

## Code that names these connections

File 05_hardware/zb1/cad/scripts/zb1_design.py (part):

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    C("C12", "4.7nF", "SHIELD", "GND", "usb"),
    dict(ref="U5", sym="Power_Protection:USBLC6-2SC6", fp=SOT23_6, value="USBLC6-2SC6",
         mpn="ST USBLC6-2SC6", block="usb",
         pins={"1": "USB_DN", "6": "USB_DN", "3": "USB_DP", "4": "USB_DP", "2": "GND", "5": "VBUS"}),

    # ------------------------------------------------------------------ charger + power path
    dict(ref="U2", sym="zb1:BQ21040", fp=SOT23_6, value="BQ21040DBVR", mpn="TI BQ21040DBVR",
         block="charger", pins={"1": "CHG_TS", "2": "VBAT", "3": "CHG_N", "4": "CHG_ISET",
                                "5": "GND", "6": "VBUS"}),
    R("R3", "1.07k", "CHG_ISET", "GND", "charger"),
    R("R4", "10k", "CHG_TS", "GND", "charger", mpn="10k 1% (or 10k NTC on the cell)"),
    C("C1", "10uF", "VBUS", "GND", "charger", fp=C0603),
    C("C2", "4.7uF", "VBAT", "GND", "charger", fp=C0603),
    dict(ref="LED2", sym="Device:LED", fp=LED0603, value="CHG orange", mpn="orange 0603 LED",
         block="charger", pins={"1": "CHG_N", "2": "CHG_LED_A"}),
    R("R21", "1k", "VBUS", "CHG_LED_A", "charger"),
    dict(ref="D1", sym="Device:D_Schottky", fp="Diode_SMD:D_SOD-123", value="B5819W",
         mpn="B5819W SOD-123", block="charger", pins={"1": "VSYS", "2": "VBUS"}),
    dict(ref="Q1", sym="Device:Q_PMOS_GSD", fp=SOT23, value="DMG3415U", mpn="Diodes DMG3415U-7",
         block="charger", pins={"1": "VBUS", "2": "VSYS", "3": "VBAT"}),
    R("R7", "100k", "VBUS", "GND", "charger"),
    C("C3", "22uF", "VSYS", "GND", "charger", fp=C0805),
    dict(ref="J3", sym="Connector_Generic:Conn_01x02",
         fp="Connector_JST:JST_PH_B2B-PH-SM4-TB_1x02-1MP_P2.00mm_Vertical", value="BATT JST-PH",
         mpn="JST B2B-PH-SM4-TB", block="charger", pins={"1": "BATN", "2": "VBAT"}),
    # optional cell protection (DNP by default; SJ2 bridges BATN to GND)
    dict(ref="U6", sym="zb1:DW01A", fp=SOT23_6, value="DW01A", mpn="Fortune DW01A", dnp=True,
         block="protect", pins={"1": "PROT_OD", "2": "PROT_CS", "3": "PROT_OC", "5": "PROT_VCC",
                                "6": "BATN"}),
    dict(ref="Q2", sym="zb1:FS8205A", fp="Package_SO:TSSOP-8_4.4x3mm_P0.65mm", value="FS8205A",
         mpn="Fortune FS8205A", dnp=True, block="protect",
         pins={"1": "PROT_D", "8": "PROT_D", "2": "BATN", "3": "BATN", "4": "PROT_OD",
               "5": "PROT_OC", "6": "GND", "7": "GND"}),
    R("R23", "100", "VBAT", "PROT_VCC", "protect", dnp=True),
    C("C13", "100nF", "PROT_VCC", "BATN", "protect", dnp=True),
    R("R24", "2k", "PROT_CS", "GND", "protect", dnp=True),
    dict(ref="SJ2", sym="Jumper:SolderJumper_2_Bridged",
         fp="Jumper:SolderJumper-2_P1.3mm_Bridged_RoundedPad1.0x1.5mm", value="PROT bypass",
         mpn="(PCB) cut if U6/Q2 fitted", block="protect", pins={"1": "BATN", "2": "GND"}),

    # ------------------------------------------------------------------ 3.3 V regulator + test hooks
    dict(ref="U3", sym="zb1:RT9080-33", fp=SOT23_5, value="RT9080-33GJ5", mpn="Richtek RT9080-33GJ5",
         block="ldo", pins={"1": "VSYS", "2": "GND", "3": "LDO_EN", "5": "3V3_LDO"}),
    R("R8", "1M", "VSYS", "LDO_EN", "ldo"),
    C("C4", "1uF", "VSYS", "GND", "ldo"),
    C("C5", "22uF", "3V3_LDO", "GND", "ldo", fp=C0805),
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         fp="Jumper:SolderJumper-2_P1.3mm_Bridged_RoundedPad1.0x1.5mm", value="I_MEAS",
         mpn="(PCB) cut to measure current", block="ldo", pins={"1": "3V3_LDO", "2": "3V3"}),
    dict(ref="TP1", sym="Connector:TestPoint", fp=TP, value="TP_EN", mpn="(PCB)", block="ldo",
         pins={"1": "LDO_EN"}),
    dict(ref="TP2", sym="Connector:TestPoint", fp=TP, value="VBAT", mpn="(PCB)", block="ldo",
         pins={"1": "VBAT"}),
    dict(ref="TP3", sym="Connector:TestPoint", fp=TP, value="VSYS", mpn="(PCB)", block="ldo",
         pins={"1": "VSYS"}),
    dict(ref="TP4", sym="Connector:TestPoint", fp=TP, value="3V3", mpn="(PCB)", block="ldo",
         pins={"1": "3V3"}),
    dict(ref="TP5", sym="Connector:TestPoint", fp=TP, value="GND", mpn="(PCB)", block="ldo",
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    C("C15", "1uF", "CHIP_EN", "GND", "mcu"),
    R("R25", "10k", "3V3", "BOOT", "mcu"),
    dict(ref="SW1", sym="Switch:SW_Push", fp="Button_Switch_SMD:SW_Push_1P1T_NO_CK_KMR2",
         value="RESET", mpn="C&K KMR221GLFS", block="mcu", pins={"1": "CHIP_EN", "2": "GND"}),
    dict(ref="SW2", sym="Switch:SW_Push", fp="Button_Switch_SMD:SW_Push_1P1T_NO_CK_KMR2",
         value="BOOT", mpn="C&K KMR221GLFS", block="mcu", pins={"1": "BOOT", "2": "GND"}),
    dict(ref="Y1", sym="Device:Crystal", fp="Crystal:Crystal_SMD_3215-2Pin_3.2x1.5mm",
         value="32.768kHz 12.5pF", mpn="Epson FC-135 32.768kHz 12.5pF", block="mcu",
         pins={"1": "XTAL32_P", "2": "XTAL32_N"}),
    C("C8", "18pF", "XTAL32_P", "GND", "mcu", mpn="18pF C0G"),
    C("C9", "18pF", "XTAL32_N", "GND", "mcu", mpn="18pF C0G"),
    dict(ref="LED1", sym="Device:LED", fp=LED0603, value="USER red", mpn="red 0603 LED",
         block="mcu", pins={"1": "GND", "2": "LED_A"}),
    R("R20", "2.2k", "LED", "LED_A", "mcu"),

    # ------------------------------------------------------------------ microSD
    dict(ref="U4", sym="Power_Management:TPS22917DBV", fp=SOT23_6, value="TPS22917DBVR",
         mpn="TI TPS22917DBVR", block="sd",
         pins={"1": "3V3", "2": "GND", "3": "SD_PWR_EN", "5": "SD_VDD", "6": "SD_VDD"}),
    R("R17", "100k", "SD_PWR_EN", "GND", "sd"),
    C("C10", "1uF", "3V3", "GND", "sd"),
    C("C11", "10uF", "SD_VDD", "GND", "sd", fp=C0603),
    dict(ref="J2", sym="Connector:Micro_SD_Card_Det_Hirose_DM3AT",
         fp="Connector_Card:microSD_HC_Hirose_DM3AT-SF-PEJM5", value="microSD push-push",
         mpn="Hirose DM3AT-SF-PEJM5", block="sd",
         pins={"1": "SD_D2", "2": "SD_D3", "3": "SD_CMD", "4": "SD_VDD", "5": "SD_CLK", "6": "GND",
               "7": "SD_D0", "8": "SD_D1", "9": "GND", "10": "SD_DET", "11": "GND"}),
    R("R15", "33", "SD_CLK_MCU", "SD_CLK", "sd"),
    R("R10", "10k", "SD_VDD", "SD_CMD", "sd"),
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    dict(ref="J5", sym="Connector_Generic:Conn_01x16",
         fp="Connector_PinHeader_2.54mm:PinHeader_1x16_P2.54mm_Vertical", value="Feather 16",
         mpn="1x16 2.54mm header (ship loose)", block="io",
         pins={"1": "CHIP_EN", "2": "3V3", "4": "GND", "5": "A0", "6": "A1", "7": "A2", "8": "A3",
               "9": "A4", "11": "SCK", "12": "MOSI", "13": "MISO", "14": "RX", "15": "TX"}),
    dict(ref="J6", sym="Connector_Generic:Conn_01x12",
         fp="Connector_PinHeader_2.54mm:PinHeader_1x12_P2.54mm_Vertical", value="Feather 12",
         mpn="1x12 2.54mm header (ship loose)", block="io",
         pins={"1": "VBAT", "2": "LDO_EN", "3": "VBUS", "4": "LED", "5": "D12", "6": "D11",
               "7": "D10", "8": "D9", "9": "D6", "10": "D5", "11": "SCL", "12": "SDA"}),
]

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

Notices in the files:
README.md:
13. Status, licence, provenance:
Status:** pre-prototype. The architecture verdict is *conditional proceed*, pending hardware
experiments E1 (link), E5 (congestion and rate control), E6 (energy) and E7 (power cuts on
real flash).
Licence:** open source, © 2026 Benjamin W. Denio, licensed in three permissive parts.
[`LICENSING.md`](LICENSING.md) says which paths each covers.
Part | Licence
Code | [Apache-2.0](LICENSES/Apache-2.0.txt)
ZB-1 hardware design | [CERN-OHL-P-2.0](LICENSES/CERN-OHL-P-2.0.txt)
Documentation, diagrams, data | [CC-BY-4.0](LICENSES/CC-BY-4.0.txt)
The
